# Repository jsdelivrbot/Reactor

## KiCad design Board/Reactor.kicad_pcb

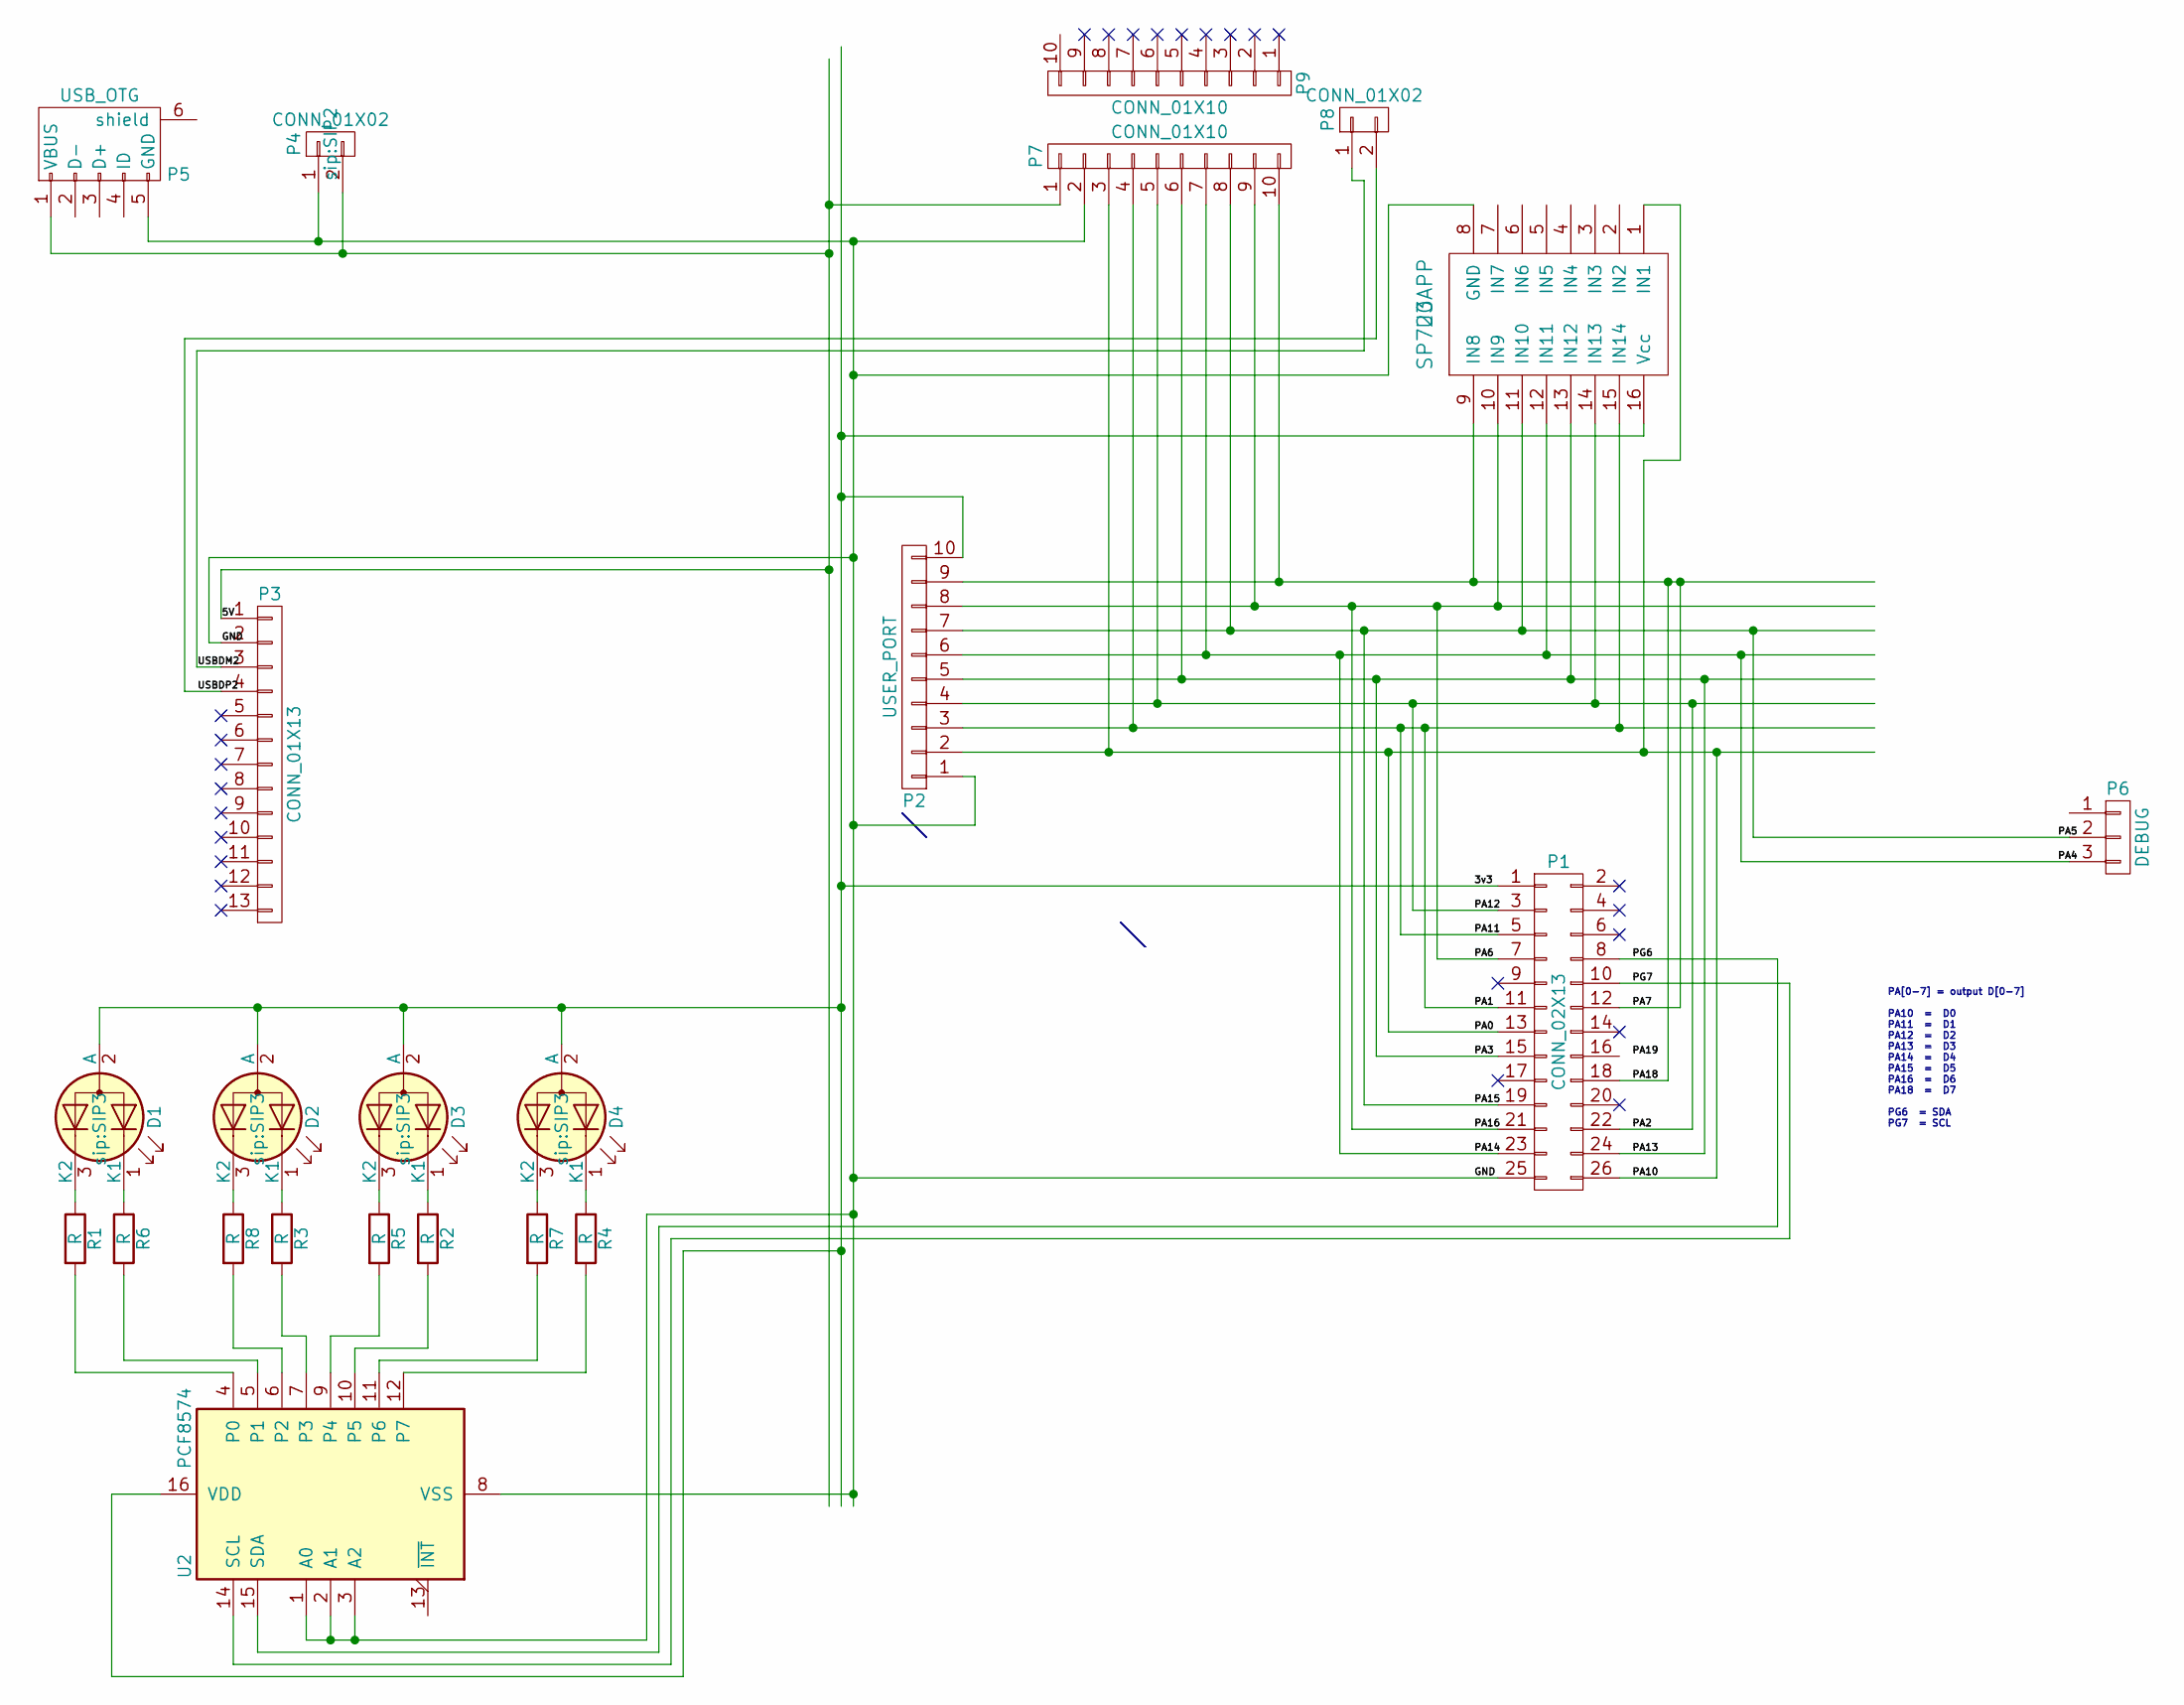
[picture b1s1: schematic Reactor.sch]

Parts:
D1, D2, D3, D4: LED_Dual_CAC; SIP3
P1: CONN_02X13; IDC_Header_Straight_26pins
P2: USER_PORT; Pin_Header_Angled_1x10_Pitch2.54mm
P3: CONN_01X13; Pin_Header_Straight_1x13_Pitch2.54mm
P4, P8: CONN_01X02; SIP2
P5: USB_OTG; MiniUSB_ThruHole_Molex_54819_0519
P6: DEBUG; Molex_KK-6410-03_03x2.54mm_Straight
P7, P9: CONN_01X10; Molex_SPOX-5267_22-03-5105_10x2.54mm_Straight
R1, R2, R3, R4, R5, R6, R7, R8: R; R_Axial_DIN0204_L3.6mm_D1.6mm_P7.62mm_Horizontal
U2: PCF8574; DIP-16_W7.62mm_LongPads
U3: SP720APP; DIP16

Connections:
/3v3: D1.2 (A), D2.2 (A), D3.2 (A), D4.2 (A), P1.1, P2.10, U2.16 (VDD), U3.16 (Vcc)
/5V: P3.1, P4.2, P5.1 (VBUS), P7.1
/GND: P1.25, P2.1, P3.2, P4.1, P5.5 (GND), P7.2, U2.1 (A0), U2.2 (A1), U2.3 (A2), U2.8 (VSS), U3.8 (GND)
/PA0: P1.13, P1.26, P2.2, P7.3, U3.1 (IN1)
/PA1: P1.5, P1.11, P2.3, P7.4, U3.15 (IN14)
/PA12: P1.3, P1.22, P2.4, P7.5, U3.14 (IN13)
/PA13: P1.15, P1.24, P2.5, P7.6, U3.13 (IN12)
/PA14: P1.23, P2.6, P6.3, P7.7, U3.12 (IN11)
/PA15: P1.19, P2.7, P6.2, P7.8, U3.11 (IN10)
/PA16: P1.7, P1.21, P2.8, P7.9, U3.10 (IN9)
/PA18: P1.12, P1.18, P2.9, P7.10, U3.9 (IN8)
/PG6: P1.8, U2.15 (SDA)
/PG7: P1.10, U2.14 (SCL)
/USBDM2: P3.3, P8.1
/USBDP2: P3.4, P8.2
unnamed: D1.1 (K1), R6.1
unnamed: D1.3 (K2), R1.1
unnamed: D2.1 (K1), R3.1
unnamed: D2.3 (K2), R8.1
unnamed: D3.1 (K1), R2.1
unnamed: D3.3 (K2), R5.1
unnamed: D4.1 (K1), R4.1
unnamed: D4.3 (K2), R7.1
unnamed: R1.2, U2.4 (P0)
unnamed: R2.2, U2.10 (P5)
unnamed: R3.2, U2.7 (P3)
unnamed: R4.2, U2.12 (P7)
unnamed: R5.2, U2.9 (P4)
unnamed: R6.2, U2.5 (P1)
unnamed: R7.2, U2.11 (P6)
unnamed: R8.2, U2.6 (P2)

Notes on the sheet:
PA[0-7] = output D[0-7] PA10 = D0 PA11 = D1 PA12 = D2 PA13 = D3 PA14 = D4 PA15 = D5 PA16 = D6 PA18 = D7 PG6 = SDA PG7 = SCL

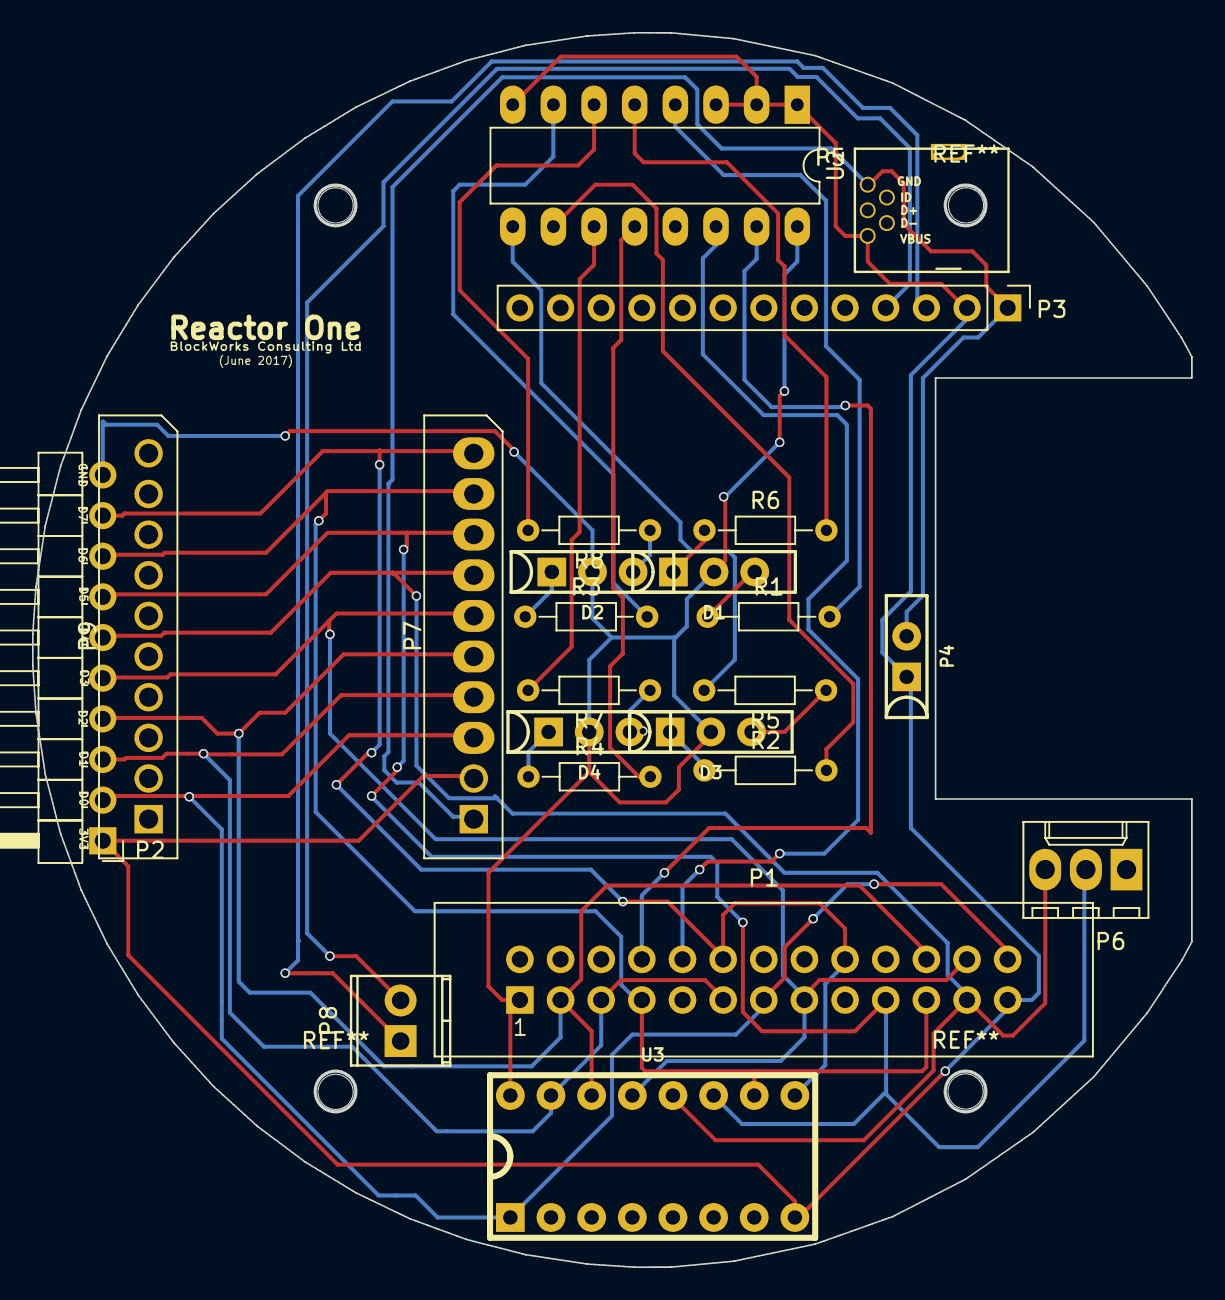
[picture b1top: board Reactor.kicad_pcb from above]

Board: 2 copper layers, 72.4 x 77.1 mm, 23 parts (0 on the bottom side), 31 nets.

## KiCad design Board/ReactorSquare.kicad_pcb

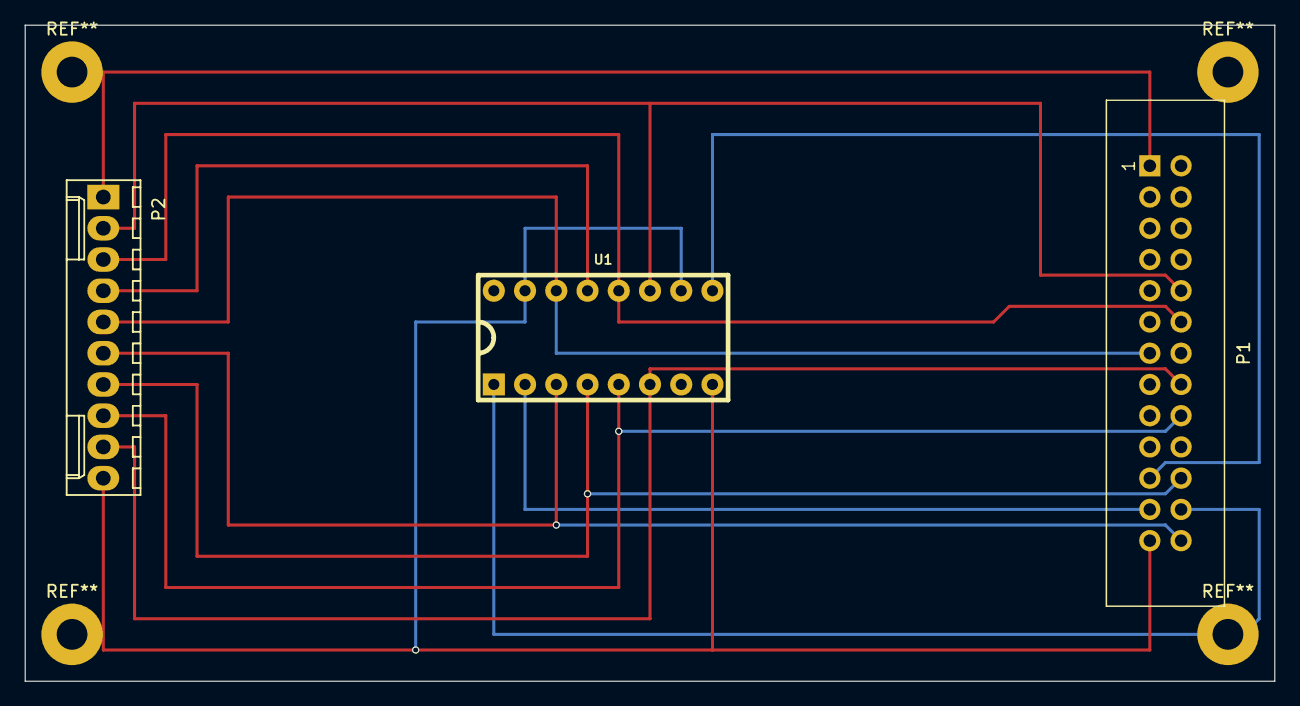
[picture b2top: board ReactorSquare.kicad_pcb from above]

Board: 2 copper layers, 101.6 x 53.3 mm, 3 parts (0 on the bottom side), 13 nets.

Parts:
P1: CONN_02X13; IDC_Header_Straight_26pins
P2: CONN_01X10; Molex_KK-6410-10_10x2.54mm_Straight
U1: 74LS165; DIP16

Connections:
+3V3: P1.1, P2.1
GND: P1.25, P2.10, U1.8, U1.10, U1.15
unnamed: P1.10, P2.2, U1.11
unnamed: P1.12, P2.3, U1.12
unnamed: P1.13, P2.5, U1.14
unnamed: P1.16, P2.9, U1.6
unnamed: P1.18, P2.8, U1.5
unnamed: P1.21, U1.9
unnamed: P1.22, P2.7, U1.4
unnamed: P1.23, U1.2
unnamed: P1.24, U1.1
unnamed: P1.26, P2.6, U1.3
unnamed: P2.4, U1.13

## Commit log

2016-12-21 - read from shift register returning correct values.
2017-01-11 - Working on prototype board! :o)
2017-01-13 - nice clean single bits identified.
2017-01-21 Changed to circular board
2017-01-25 gerber generated
2017-01-25 Gerbers regenerated
2017-01-26 - All ready for manufacture I think.
2017-01-27 Case is coming together now
2017-01-28 - Added bottom and posts.
2017-01-29 shm all hooked up in Control/Inlet/Outlet
2017-01-29 circularbuffer implemented but not working yet.
2017-01-30 CircularBuffers in shared memory working to some degree.
2017-01-31 CircularBuffer now working.
2017-02-01 Changed the startup sync.
2017-02-01 InletToControl working well.
2017-02-01 Both circular buffers working well
2017-02-02 Added memory barriers and more syncing.
2017-02-03 Added Server.
2017-02-03 Added Build.sh
2017-02-03 - Server taking input from Control.
2017-02-05 Comms Working well and case modded for bottom.
2017-02-05 Work on case
2017-02-05 INput from shift register now being timestamped and moved over to Control core.
2017-02-05 Output now being controlled from Control core and being read back correctly from Inlet core into Control core.
2017-02-06 loopback change test output->input
2017-02-15 bit banging shift register driver now.
2017-02-17 Working on the real board (Reactor One) with new front end loop.
2017-02-17 missed Comnon stuff
2017-02-17 Optimised s/w shift reg driver further.
2017-02-17 Back onto h/w SPI shit reg driver
2017-02-18 LEDs
2017-02-18 LED display working! :o)
2017-02-18 LEDs working with while outputting data now.
2017-02-19 high rate SPI clock but with 1.7uS gaps every 64 bytes.
2017-02-19 s/w CS and h/w SPI CLK... sort of works
2017-02-19 25MHz SPI clk with 1.5uS gaps every 64 bytes
2017-02-20 pwm0 now outputs a 24mhz clk
2017-02-22 clocks good, but nothing from shiftreg.
2017-02-24 Signs of life again. (s/w generated signal)
2017-02-24 Still getting input while in Inlet.
2017-02-24 - still working
2017-02-24 - still working with PWM as CLK and new PL
2017-02-25 - gone bad
2017-02-25 Working again. shift reg outputs pattern.
2017-02-25 working while being clocked by PWM0
2017-02-25 still working.
2017-02-25 Added Case3.stl
2017-02-25 working still
2017-02-25 needs an extra CTL setting to make it reliable.
2017-02-25 data out from shift reg needs to go into MOSI, not MISO in slave mode.
2017-02-26 continuous clock gets >2MHz sampling in Inlet
2017-02-26 Outlet is now performing the parallel-load and Inlet just reads SPI FIFO.
2017-02-27 Getting input from shift register with PWM and SPI slave.
2017-02-28 still working at 1MHz
2017-02-28 still working at 2MHz
2017-02-28 Gettin the new plumbing in place.
2017-03-01 Patched board for new D0
2017-03-01 working at slower clock rate,
2017-03-02 still working quite cleanly.
2017-03-06 Started new design without shift register but with I2C I/O expander and direct I/O reads
2017-03-07 read & write @ 9MHz each
2017-03-07 Changing over to c++17
2017-03-08 Moved to a template FastSharedBuffer.
2017-03-08 volatile slows things down quite a bit.
2017-03-08 gets stuck when rate limiting turned on in shared buffer
2017-03-08 memory barriers work wonders
2017-03-09 adding msync is slow but reliable.
2017-03-10 fixed issue with sharedbuffer size
2017-03-10 FastSharedBuffer working nicely now.
2017-03-12 - board laid out (draft).
2017-03-12 - Working pretty good.
2017-03-13 WOrking nicely. key is to give the fastbuffers enough space to reduce contention.
2017-03-13 Added Scheduler & 8xUARTReceiver8N1s. Runs @ ~4MHz
2017-03-13 Forgotten file
2017-03-13 - first attempt at I2CMaster.
2017-03-15 Using CNT64 for better timing and getting PWM working.
2017-03-15 can generate a 3MHz clock
2017-03-15 Timing working nicely for PWM @ 1KHz
2017-03-15 Working again but only if DebugPrintf in loop.
2017-03-16 missing volatile on counter read found
2017-03-16 24MHz CNT64 working but slow access.
2017-03-16 added CPU freq monitoring and setting
2017-03-19 Tidying up Makefiles
2017-03-19 added .gitignore
2017-03-19 First attempt at scheduler alg.
2017-03-21 Got the Scheduler.py working for a trivial timeslot allocation scheme.
2017-03-21 Getting code generation working.
2017-03-21 Generating and building scheduler from channel config now
2017-03-22 - trying to get the scheduler timeing correct.
2017-03-23 Timing test: relatively stable 3MHz square wave generated in s/w
2017-03-23 Timing test: relatively stable 1MHz square wave generated in s/w
2017-03-24 generating 8x1MHz streams.
2017-03-24 7xI2CMasters and 1x1MHz clock
2017-03-25 I2CMaster now triggers correctly
2017-03-25 I2CMaster working nicely
2017-03-25 Using FastSharedBuffer for I2C data
2017-03-25 1MHz clock and I2C master being triggered from Server core.
2017-03-27 Getting command queue working.
2017-03-27 Added PCF8574
2017-03-27 command queue almost working.
2017-03-28 Correct number of bytes being transmitted for I2C now
2017-03-30 Moved timing loop to Inlet to throttle data at source.
2017-03-30 working ok again.
2017-03-30 Added more I2C activity channels
2017-03-31 - LED is flashing from PCF8574AP
2017-03-31 tricolour LEDs gicing a show now.
2017-04-19 Moving FTDI code into Server
2017-04-19 Builds with FTDI stuff now
2017-04-19 Moved Server to CPU0 for IRQ affinity purposes
2017-04-19 Added IRQ affinity stuff.
2017-04-19 FTDIDataSource now working in Server
2017-04-19 ftdi buffering figured out now.
2017-04-19 Setting FT232H mode so can read bits from pins
2017-04-19 40MB/sec and reading values correctly.
2017-04-20 - Change to async bitbang mode with baud rate of 40MBaud
2017-04-22 - Added CursesUI
2017-04-22 -refactoring
2017-04-22 - added keyboard monitoring
2017-04-22 - added toggle pause
2017-04-22 - Added TCPServer (echo server for now).
2017-04-22 Moved TCPServer to c++
2017-04-23 - simple TCP serving now
2017-04-23 Adding TCPClient
2017-04-23 - can see bits changing on CursesUI from FT232H :o)
2017-04-24 - Added Dockerfile for armbuild
2017-04-26 - Forgot to put the FTDI into input mode! Doh!
2017-04-26 - made tcp reconnects happen
2017-04-30 - Getting PCB ready for manufacture
2017-04-30 PCB stuff and tidy up
2017-04-30 - gerbers
2017-05-02 Moving to sockets instead of FT232h symbol
2017-05-03 - Added Dependencies.txt while setting up new laptop
2017-05-03 Cross compile of libusb-1.0 done.
2017-05-03 - removed unneeded files
2017-05-03 - Dockerfile now installing toolchains.
2017-05-03 - pyc
2017-05-10 Docker container now builds everything apart from libusb stuff.
2017-05-10 - Docker build now completes everything.
2017-06-12 Added Platform (BuildRoot 2017.05)
2017-06-12 Added .config for BuildRoot.
2017-06-12 modified .config
2017-06-13 BuildRoot completes ok
2017-06-20 Generated Gerbers for next spin
2017-06-20 made Gerber .zip
2017-06-20 shrunk pads on ftdi module to prevent shorts
2017-06-20 shrunk pads on ftdi module to prevent shorts. added gerber zip
2017-07-11 Added the channel for the IOExpander.
2017-07-11 - Adding the io expander demo code to server.
2017-07-13 LEDs are live!
2017-07-13 - LED colours correct now
2017-07-13 Nice LED pattern
2017-07-14 Removed printfs
2017-07-18 Testing of new board
2017-07-20 Fixed bad tracks
2017-07-29 patching uboot for mmc card detect issues
2017-07-29 Added patch to uboot to remove check for mmc card detect.
2017-07-30 added missing .d directories because of .gitignore rule
2017-08-02 Added patch to create and use reactor_defconfig
2017-08-04 adding linux.patch for opi zero dts
2017-08-04 Made uboot dts build.
2017-08-05 Made the 3v3 regulator turn on at boot (for mmc detect pullup problem). Added possible fix for emac.
2017-08-05 attemp at fixing emac again
2017-08-05 Added a Linux.config file
2017-08-05 Removed rootdelay.
2017-08-05 made root ro on boot
2017-08-06 added new emac with int_mii_phy to dt.
2017-08-06 corrected linux.patch to enable emac
2017-08-07 Added patches for sun8i-emac to the linux.patch.
2017-08-07 More patches for enabling sun8i-emac
2017-08-08 Added dhcp & net tools.
2017-08-08 can ssh into the platform now.
2017-08-08 added dropbear host key
2017-08-08 Chnanged to glibc so the Reactor binaries are executable
2017-08-09 added key
2017-08-09 added network interfaces to stop random MAC address
2017-08-09 Removed MessageBox unused code
2017-08-09 Forked enable_arm_pmu to cross-compile it
2017-08-09 added MakeMe for pmu module
2017-08-09 using the buildroot compiler instead...
2017-08-10 Started the management interface.
2017-08-11 Initial commit of ManagementInterface
2017-08-13 bit of work on MI
2017-08-14 adding extra data partition
2017-08-14 Added MakeDiskImage.sh
2017-08-14 MakeDiskImage work
2017-08-14 NOw can use MakeDiskImage script to get partitions and read-only root.
2017-08-15 platform image now working with copy of rootfs.ext4
2017-08-15 MakeDiskImage still works
2017-08-15 Added some lighttpd setup
2017-08-16 Added Management Interface
2017-08-16 corrected paths in html.
2017-08-16 Got the .ko building
2017-08-16 added ko build to Build.sh and Install.sh
2017-08-16 corrected install script
2017-08-16 Fixed owner in rootfs
2017-08-23 Changed LED pattern...
2017-08-29 added fix for avahi startup issue
2017-08-29 Made the hostname dynamic
2017-08-29 Made the MAC address configurable from /etc/MAC and also used for hostname for .local resolution
2017-08-29 added zerconf service descriptors
2017-08-30 made replacement for pkill
2018-12-08 Replace RawGit with jsDelivr
